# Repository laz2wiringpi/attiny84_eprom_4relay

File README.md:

# attiny84_eprom_4relay
attiny84 4 button eprom relay

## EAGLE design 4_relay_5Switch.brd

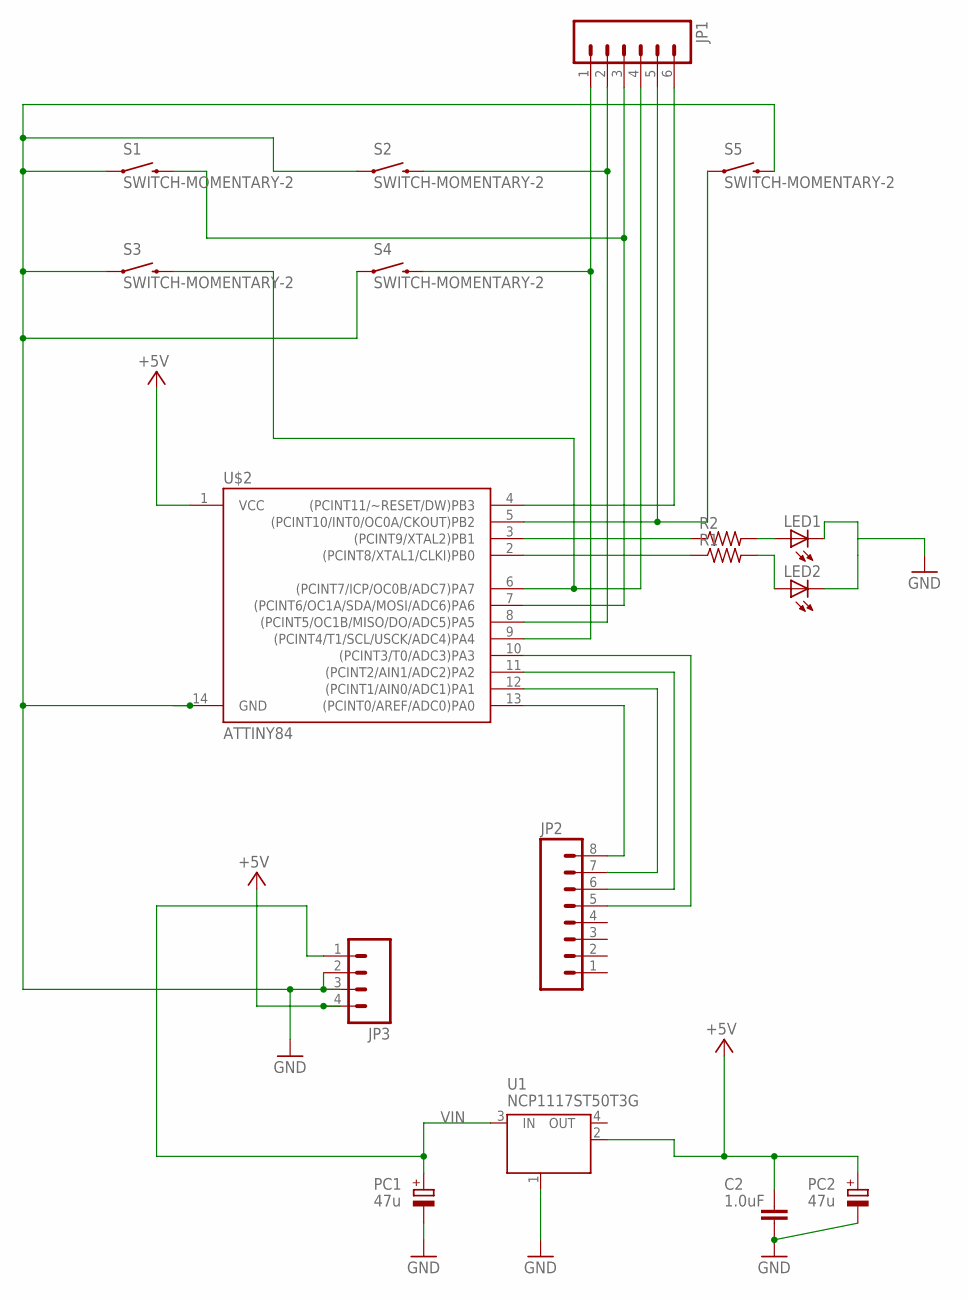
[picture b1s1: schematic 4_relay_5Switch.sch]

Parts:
C2: 1.0uF; 0805
JP1: M06NO_SILK_FEMALE_PTH; 1X06_NO_SILK
JP2: M08NO_SILK; 1X08_PIN1_NO_SILK
JP3: M041X04_NO_SILK; 1X04_NO_SILK
LED1, LED2: LEDCHIP-LED0805; CHIP-LED0805
PC1, PC2: 47u; E2,5-4R
R1, R2: R-US_R0805; R0805
S1, S2, S3, S4, S5: SWITCH-MOMENTARY-2; TACTILE_FSM4JSMATR
U1: NCP1117ST50T3G; SOT223
U$2: ATTINY84; SO14

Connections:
+5V: C2.2, JP3.4, PC2.+, U1.2 (OUT), U$2.1 (VCC)
GND: C2.1, JP3.2, JP3.3, LED1.C, LED2.C, PC1.-, PC2.-, S1.P$1 (1), S1.P$2 (1), S2.P$1 (1), S2.P$2 (1), S3.P$1 (1), S3.P$2 (1), S4.P$1 (1), S4.P$2 (1), S5.P$3 (2), S5.P$4 (2), U1.1 (GND/ADJ), U$2.14 (GND)
unnamed: JP1.2, S2.P$3 (2), S2.P$4 (2), U$2.8 ((PCINT5/OC1B/MISO/DO/ADC5)PA5)
unnamed: JP1.6, U$2.4 ((PCINT11/~RESET/DW)PB3)
unnamed: JP1.1, S4.P$3 (2), S4.P$4 (2), U$2.9 ((PCINT4/T1/SCL/USCK/ADC4)PA4)
unnamed: JP2.8, U$2.13 ((PCINT0/AREF/ADC0)PA0)
unnamed: JP1.3, S1.P$3 (2), S1.P$4 (2), U$2.7 ((PCINT6/OC1A/SDA/MOSI/ADC6)PA6)
unnamed: JP2.7, U$2.12 ((PCINT1/AIN0/ADC1)PA1)
unnamed: JP2.6, U$2.11 ((PCINT2/AIN1/ADC2)PA2)
unnamed: JP2.5, U$2.10 ((PCINT3/T0/ADC3)PA3)
unnamed: JP1.4, S3.P$3 (2), S3.P$4 (2), U$2.6 ((PCINT7/ICP/OC0B/ADC7)PA7)
unnamed: JP1.5, S5.P$1 (1), S5.P$2 (1), U$2.5 ((PCINT10/INT0/OC0A/CKOUT)PB2)
unnamed: R2.1, U$2.3 ((PCINT9/XTAL2)PB1)
unnamed: R1.1, U$2.2 ((PCINT8/XTAL1/CLKI)PB0)
unnamed: LED1.A, R2.2
unnamed: LED2.A, R1.2
VIN: JP3.1, PC1.+, U1.3 (IN)

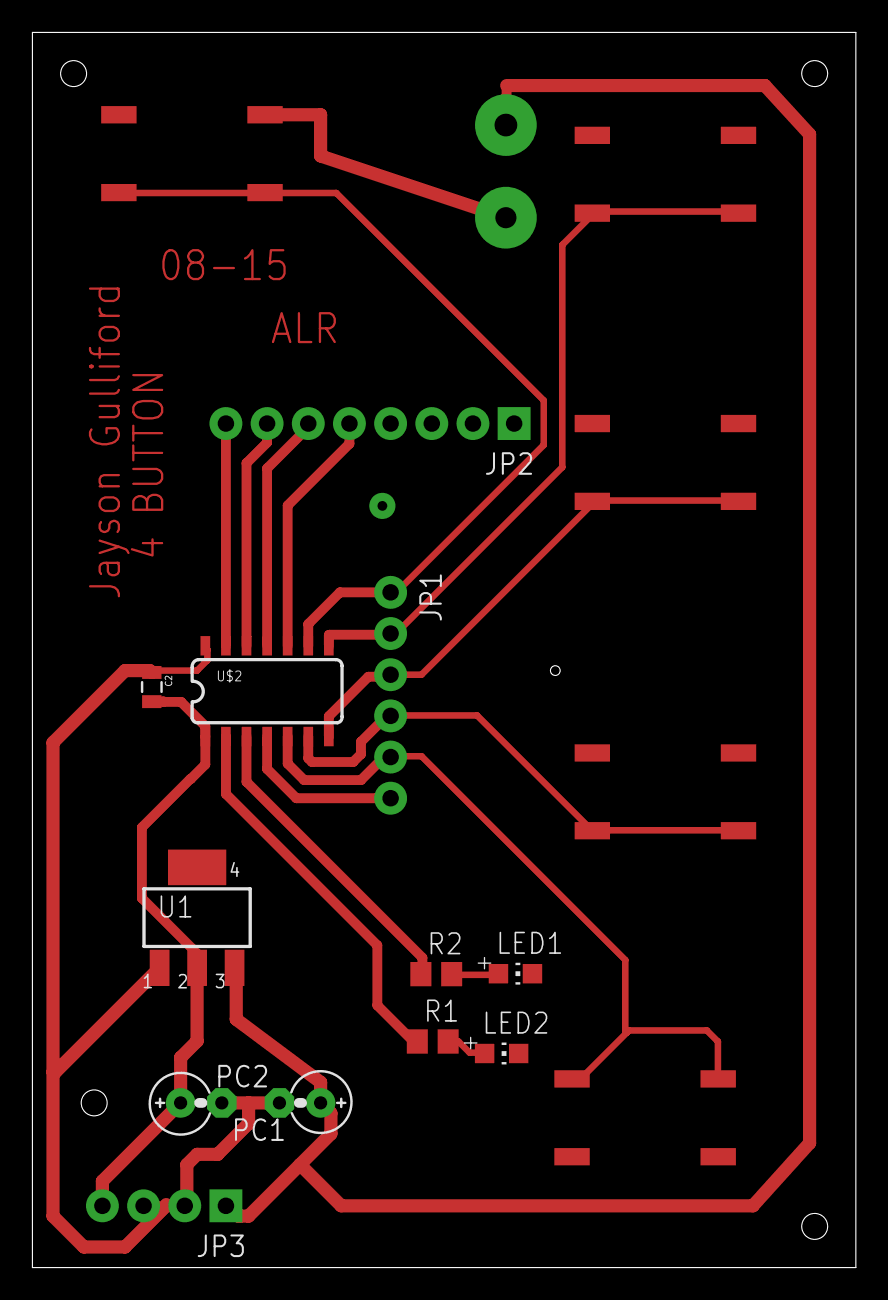
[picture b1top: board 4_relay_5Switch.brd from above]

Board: 2 copper layers, 50.8 x 76.2 mm, 17 parts (0 on the bottom side), 17 nets.

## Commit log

2015-08-27 init
    init
2015-08-27 add file
2015-09-01 working on
2015-09-08 fail git
2015-09-09 RESTORE
2015-09-09 CLEAN UP

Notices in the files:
parts and their libraries:
SparkFun-Electromechanical_alr: Licensing: Creative Commons ShareAlike 4.0 International - https://creativecommons.org/licenses/by-sa/4.0
